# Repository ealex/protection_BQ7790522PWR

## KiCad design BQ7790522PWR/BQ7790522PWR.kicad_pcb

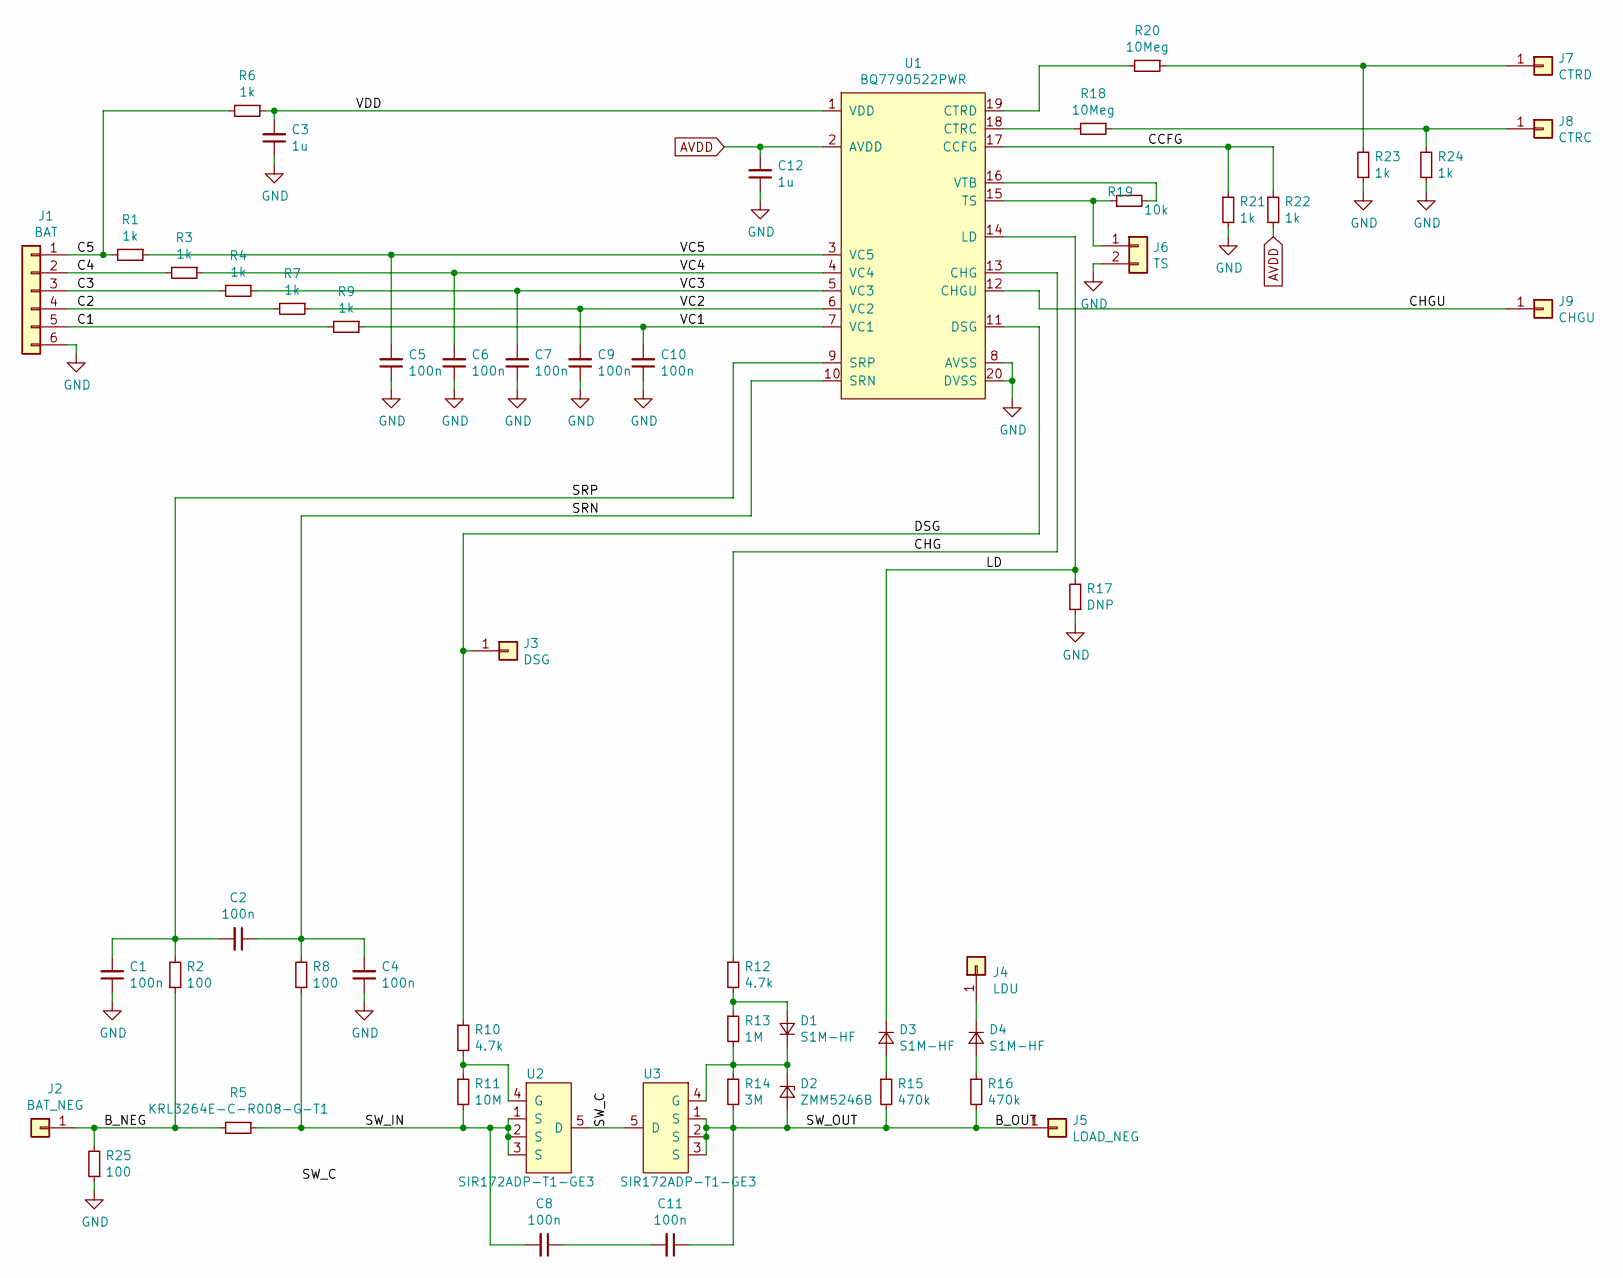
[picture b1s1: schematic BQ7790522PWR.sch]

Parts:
C1, C2, C4, C5, C6, C7, C8, C9, C10, C11: 100n; C_0805_2012Metric
C3, C12: 1u; C_0805_2012Metric
D1, D3, D4: S1M-HF; D_SMA
D2: ZMM5246B; D_MiniMELF
J1: BAT; JST_PH_B6B-PH-K_1x06_P2.00mm_Vertical
J2: BAT_NEG; PTH_M3
J3: DSG; PinHeader_1x01_P2.54mm_Vertical
J4: LDU; PinHeader_1x01_P2.54mm_Vertical
J5: LOAD_NEG; PTH_M3
J6: TS; PinHeader_1x02_P2.54mm_Vertical
J7: CTRD; PinHeader_1x01_P2.54mm_Vertical
J8: CTRC; PinHeader_1x01_P2.54mm_Vertical
J9: CHGU; PinHeader_1x01_P2.54mm_Vertical
R1, R3, R4, R6, R7, R9, R21, R22, R23, R24: 1k; R_0805_2012Metric
R2, R8, R25: 100; R_0805_2012Metric
R5: KRL3264E-C-R008-G-T1; R_2512_6332Metric
R10, R12: 4.7k; R_0805_2012Metric
R11: 10M; R_0805_2012Metric
R13: 1M; R_0805_2012Metric
R14: 3M; R_0805_2012Metric
R15, R16: 470k; R_0805_2012Metric
R17: DNP; R_0805_2012Metric
R18, R20: 10Meg; R_0805_2012Metric
R19: 10k; R_0805_2012Metric
U1: BQ7790522PWR; TSSOP-20_4.4x6.5mm_P0.65mm
U2, U3: SIR172ADP-T1-GE3; PowerPAK_SO-8_Single

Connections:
/B_NEG: J2.1, R2.1, R5.2, R25.2
/B_OUT: C11.1, D2.2 (A), J5.1, R14.2, R15.2, R16.2, U3.1 (S), U3.2 (S), U3.3 (S)
/C1: J1.5, R9.2
/C2: J1.4, R7.2
/C3: J1.3, R4.2
/C4: J1.2, R3.2
/C5: J1.1, R1.2, R6.2
/CCFG: R21.1, R22.1, U1.17 (CCFG)
/CHG: R12.1, U1.13 (CHG)
/CHGU: J9.1, U1.12 (CHGU)
/DSG: J3.1, R10.1, U1.11 (DSG)
/LD: D3.1 (K), R17.2, U1.14 (LD)
/SRN: C2.1, C4.2, R8.2, U1.10 (SRN)
/SRP: C1.2, C2.2, R2.2, U1.9 (SRP)
/SW_C: U2.5 (D), U3.5 (D)
/SW_IN: C8.2, R5.1, R8.1, R11.2, U2.1 (S), U2.2 (S), U2.3 (S)
/VC1: C10.2, R9.1, U1.7 (VC1)
/VC2: C9.2, R7.1, U1.6 (VC2)
/VC3: C7.2, R4.1, U1.5 (VC3)
/VC4: C6.2, R3.1, U1.4 (VC4)
/VC5: C5.2, R1.1, U1.3 (VC5)
/VDD: C3.2, R6.1, U1.1 (VDD)
AVDD: C12.2, R22.2, U1.2 (AVDD)
GND: C1.1, C3.1, C4.1, C5.1, C6.1, C7.1, C9.1, C10.1, C12.1, J1.6, J6.2, R17.1, R21.2, R23.1, R24.1, R25.1, U1.8 (AVSS), U1.20 (DVSS)
unnamed: C8.1, C11.2
unnamed: D1.1 (K), D2.1 (K), R13.2, R14.1, U3.4 (G)
unnamed: D1.2 (A), R12.2, R13.1
unnamed: D3.2 (A), R15.1
unnamed: D4.1 (K), J4.1
unnamed: D4.2 (A), R16.1
unnamed: J6.1, R19.1, U1.15 (TS)
unnamed: J7.1, R20.1, R23.2
unnamed: J8.1, R18.1, R24.2
unnamed: R10.2, R11.1, U2.4 (G)
unnamed: R18.2, U1.18 (CTRC)
unnamed: R19.2, U1.16 (VTB)
unnamed: R20.2, U1.19 (CTRD)

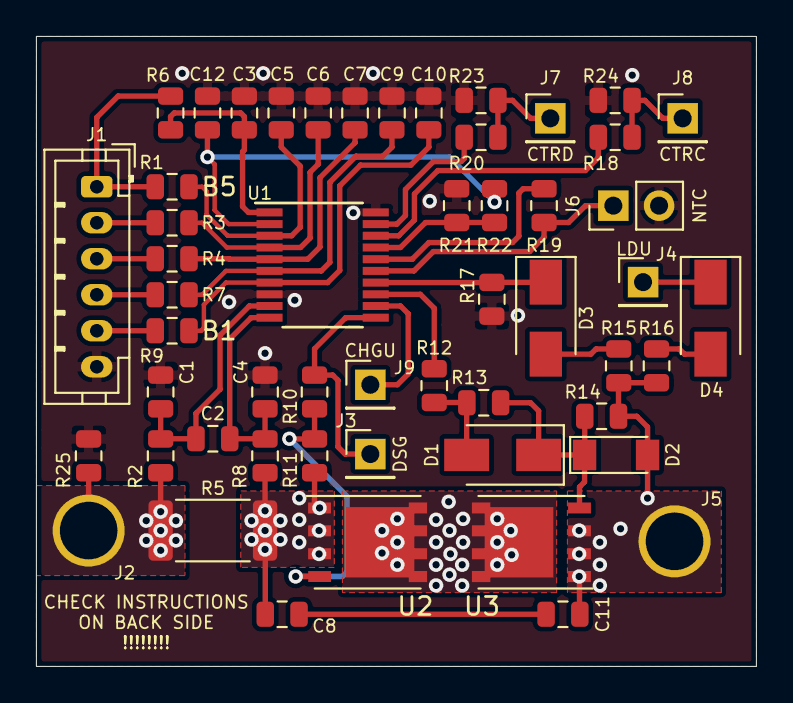
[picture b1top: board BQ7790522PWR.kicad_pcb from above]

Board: 2 copper layers, 40.0 x 35.0 mm, 53 parts (0 on the bottom side), 37 nets.

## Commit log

2022-06-15 add docs for chosen components
2022-06-15 update docs
2022-06-15 add schematic and layout
2022-06-17 update schematic and pcb
2022-06-25 create interactive BOM and order all parts
